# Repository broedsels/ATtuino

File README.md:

# ATtuino
The smaller Arduino project board

Based around an ATtiny and a tiny programmer.

V1.0
The first version to be sold on Kickstarter.
It is designed with PTH components only for easy soldering.

V2.0 beta
Changed all components to SMD components. 
Used the standard 6-pin ISP connector.

The programmer part is based upon the V-usb firmware and Design found here: https://tequals0.wordpress.com/2011/09/26/attiny45-based-usbtinyisp-programmer/

The USBtiny software is licensed under the terms of the GNU General Public License as published by the Free Software Foundation, either version 2 of the license, or (at your option) any later version.
http://dicks.home.xs4all.nl/avr/usbtiny/

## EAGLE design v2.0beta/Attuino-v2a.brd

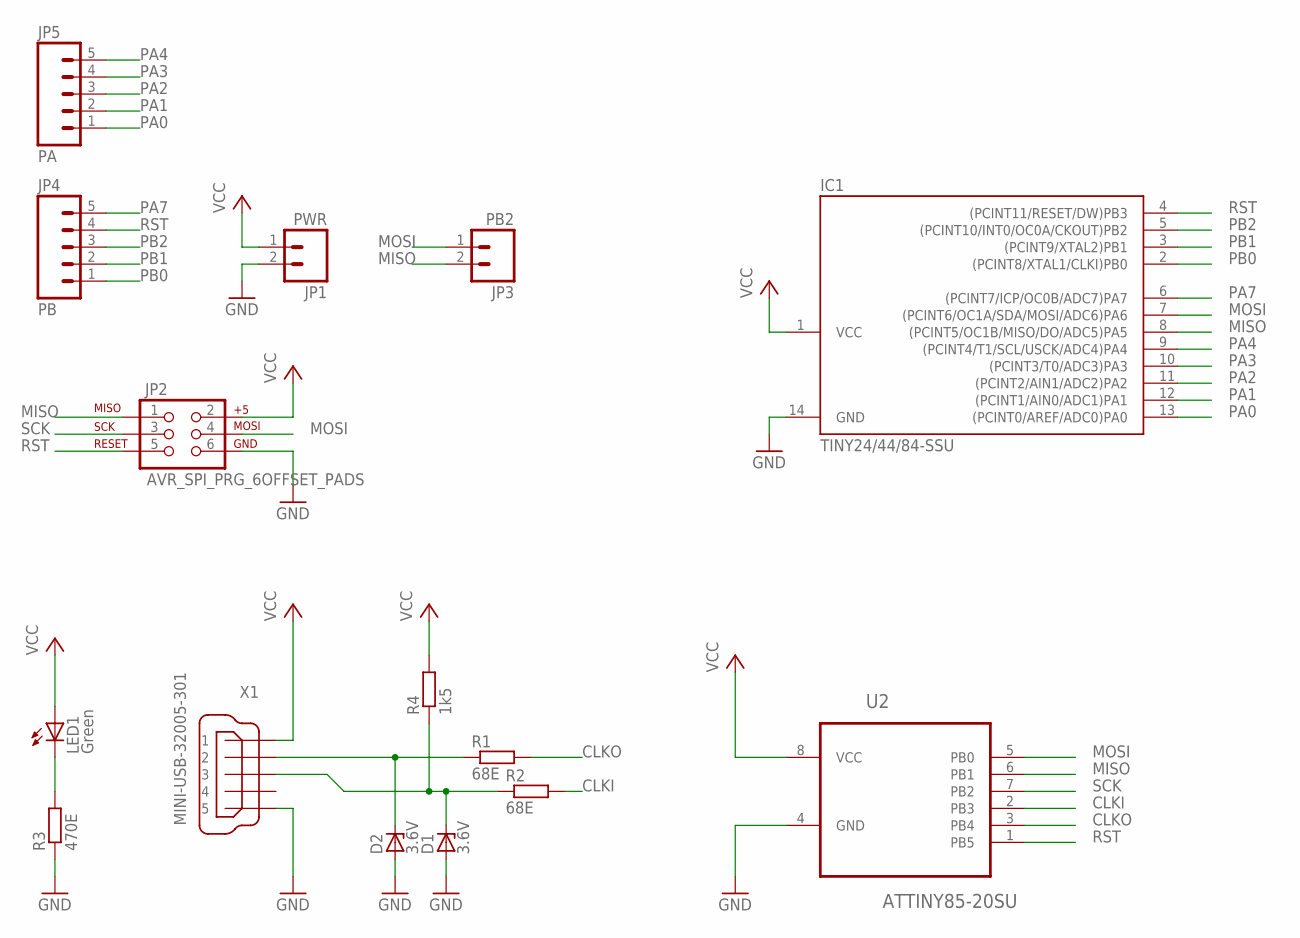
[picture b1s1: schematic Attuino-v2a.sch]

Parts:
D1, D2: 3.6V; SOD80C
IC1: TINY24/44/84-SSU; SOIC14
JP1: PWR; 1X02_NO_SILK
JP2: AVR_SPI_PRG_6OFFSET_PADS; 2X3_OFFSET
JP3: PB2; 1X02_NO_SILK
JP4: PB; 1X05_NO_SILK
JP5: PA; 1X05_NO_SILK
LED1: Green; LED_1206
R1, R2: 68E; R0805
R3: 470E; R0805
R4: 1k5; R0805
U2: ATTINY85-20SU; SOIC127P798X216-8N
X1: MINI-USB-32005-301; 32005-301

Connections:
CLKI: R2.2, U2.2 (PB3)
CLKO: R1.2, U2.3 (PB4)
GND: D1.A, D2.A, IC1.14 (GND), JP1.2, JP2.6, R3.1, U2.4 (GND), X1.5
MISO: IC1.8 ((PCINT5/OC1B/MISO/DO/ADC5)PA5), JP2.1, JP3.2, U2.6 (PB1)
MOSI: IC1.7 ((PCINT6/OC1A/SDA/MOSI/ADC6)PA6), JP2.4, JP3.1, U2.5 (PB0)
unnamed: D2.C, R1.1, X1.2
unnamed: D1.C, R2.1, R4.1, X1.3
unnamed: LED1.C, R3.2
PA0: IC1.13 ((PCINT0/AREF/ADC0)PA0), JP5.1
PA1: IC1.12 ((PCINT1/AIN0/ADC1)PA1), JP5.2
PA2: IC1.11 ((PCINT2/AIN1/ADC2)PA2), JP5.3
PA3: IC1.10 ((PCINT3/T0/ADC3)PA3), JP5.4
PA4: IC1.9 ((PCINT4/T1/SCL/USCK/ADC4)PA4), JP5.5
PA7: IC1.6 ((PCINT7/ICP/OC0B/ADC7)PA7), JP4.5
PB0: IC1.2 ((PCINT8/XTAL1/CLKI)PB0), JP4.1
PB1: IC1.3 ((PCINT9/XTAL2)PB1), JP4.2
PB2: IC1.5 ((PCINT10/INT0/OC0A/CKOUT)PB2), JP4.3
RST: IC1.4 ((PCINT11/RESET/DW)PB3), JP2.5, JP4.4, U2.1 (PB5)
SCK: JP2.3, U2.7 (PB2)
VCC: IC1.1 (VCC), JP1.1, JP2.2, LED1.A, R4.2, U2.8 (VCC), X1.1

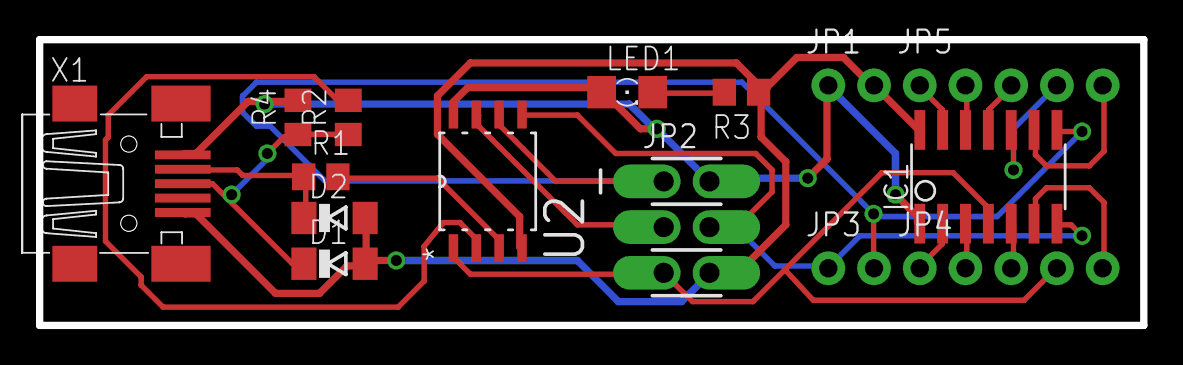
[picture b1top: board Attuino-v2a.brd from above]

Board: 2 copper layers, 61.3 x 15.9 mm, 15 parts (0 on the bottom side), 20 nets.

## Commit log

2015-06-24 v2.0 beta
    Changed the board from PTH to SMD
2015-06-24 Added discription
2015-06-25 Added hex file
2015-06-26 Picture v1
    Changed the readme and added a picture of V1.0

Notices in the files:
parts and their libraries:
SparkFun-Connectors: Licensing: Creative Commons ShareAlike 4.0 International - https://creativecommons.org/licenses/by-sa/4.0
